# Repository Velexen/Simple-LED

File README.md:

# ESP-LED

A custom ESP32-based LED controller that integrates with Home Assistant over Wi-Fi. The device controls two independent LED strips and exposes them as separate light entities in Home Assistant, allowing full smart-home control.

## Purpose

The goal of this project is to build a DIY smart LED controller from scratch — including custom PCB hardware, firmware, and home automation integration — without relying on off-the-shelf solutions.

## Features

- Controls two independent LED strips
- Wi-Fi connectivity for remote control
- Home Assistant integration (appears as two distinct light entities)
- Main power switch and a strip-selector switch
- Custom 4-layer PCB design (schematics in [schematics/](schematics/))

## Hardware

The PCB was designed in Altium Designer. Design files are located in [schematics/ESP-LED/](schematics/ESP-LED/). A pinout reference sheet is available at [schematics/Pinout.xlsx](schematics/Pinout.xlsx).

Key components:
- ESP32 microcontroller
- MOSFETs for LED switching (see `MosFets.SchDoc`)
- 5V/12V power input (see `Power.SchDoc`)

## Firmware

Built with **ESP-IDF** (Espressif IoT Development Framework). Source code lives in [src/](src/).

A code rework is currently in work under the branch "code-redo"

## Getting Started

1. Install [ESP-IDF](https://docs.espressif.com/projects/esp-idf/en/latest/esp32/get-started/)
2. Clone this repo
3. Set your Wi-Fi credentials in `src/main/wifi.c`
4. Build and flash:
   ```
   idf.py build flash monitor
   ```

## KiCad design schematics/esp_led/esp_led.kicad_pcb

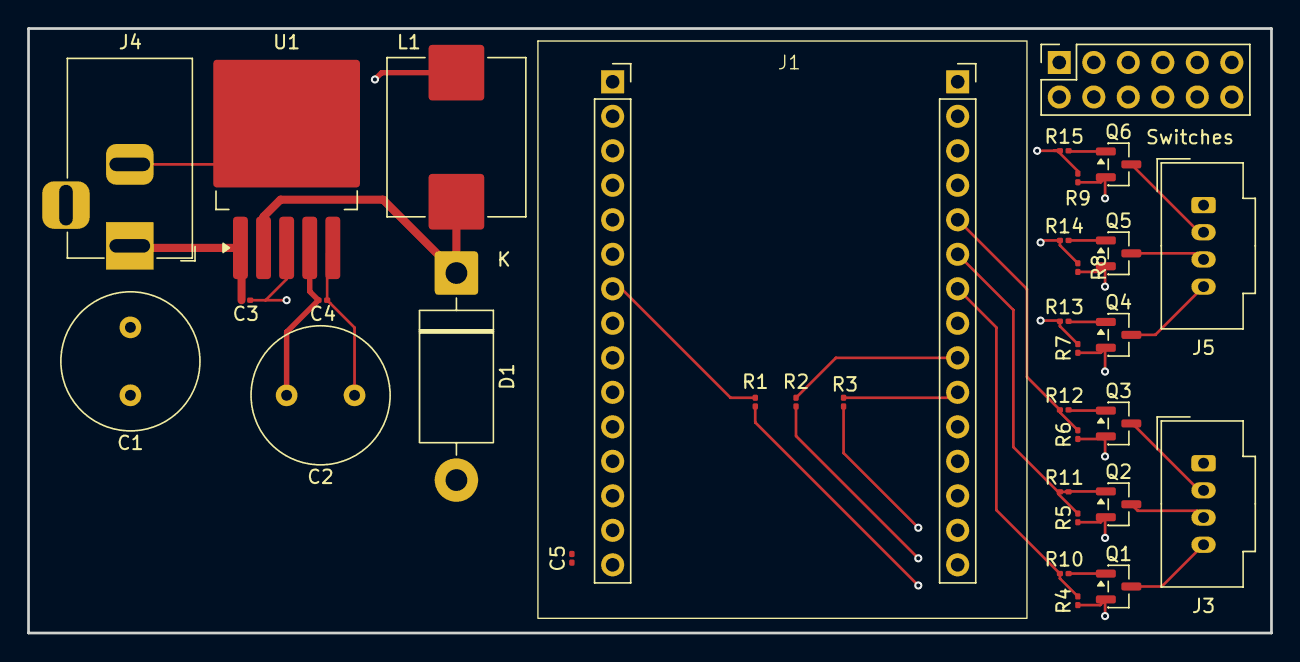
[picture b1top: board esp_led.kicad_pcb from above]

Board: 4 copper layers, 91.5 x 44.5 mm, 34 parts (0 on the bottom side), 27 nets.

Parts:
C1, C2: 470uF; C_Radial_D10.0mm_H16.0mm_P5.00mm
C3, C4, C5: 100nF; C_0201_0603Metric
D1: 1N5824; D_DO-201AD_P15.24mm_Horizontal
J1: ESP32-WROOM-DevKit; ESP32-32-Devkit-30-Pin
J3, J5: BOOMELE PH-4A; Molex_MicroClasp_55932-0430_1x04_P2.00mm_Vertical
J4: DC-005C-20A; BarrelJack_Horizontal
L1: 68μH; L_Sunlord_MWSA1005S
Q1, Q2, Q3, Q4, Q5, Q6: FDV303N; SOT-23
R1, R2, R3, R4, R5, R6, R7, R8, R9: 10kΩ; R_0201_0603Metric
R10, R11, R12, R13, R14, R15: 100Ω; R_0201_0603Metric
Switches: PinSocket_2x06_P2.54mm_Vertical
U1: LM2596S-5; TO-263-5_TabPin3

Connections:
+3V3: J1.16 (+3V3), R1.2, R2.2, R3.2, Switches.5, Switches.7, Switches.8, Switches.9, Switches.10
+5V: C2.1, C4.1, C5.1, J1.15 (VIN), L1.2, U1.4 (FB)
+24V: C1.1, C3.1, J4.1, Switches.11, U1.1 (VIN)
/Blue_1: J3.4, Q1.3 (D)
/Blue_2: J5.4, Q4.3 (D)
/Buck-Out: D1.1 (K), L1.1, U1.2 (OUT)
/Green_1: J3.2, Q3.3 (D)
/Green_2: J5.2, Q6.3 (D)
/Red_1: J3.3, Q2.3 (D)
/Red_2: J5.3, Q5.3 (D)
BLUE_PWM: J1.24 (IO18), R4.2, R10.1
BLUE_PWM_2: J1.10 (IO27), R7.2, R13.1
Color_Btn: J1.22 (IO17), R2.1
GND: C1.2, C2.2, C3.2, C4.2, C5.2, D1.2 (A), J1.14 (GND), J4.2, Q1.2 (S), Q2.2 (S), Q3.2 (S), Q4.2 (S), Q5.2 (S), Q6.2 (S), R4.1, R5.1, R6.1, R7.1, R8.1, R9.1, Switches.1, Switches.2, Switches.3, Switches.4, Switches.6, U1.3 (GND), U1.5 (~ON/OFF)
GREEN_PWM: J1.26 (IO21), R6.2, R12.1
GREEN_PWM_2: J1.8 (IO25), R9.2, R15.1
LED_24V: J3.1, J5.1, Switches.12
Main_Switch: J1.7 (IO33), R1.1
unnamed: Q1.1 (G), R10.2
unnamed: Q2.1 (G), R11.2
unnamed: Q3.1 (G), R12.2
unnamed: Q4.1 (G), R13.2
unnamed: Q5.1 (G), R14.2
unnamed: Q6.1 (G), R15.2
RED_PWM: J1.25 (IO19), R5.2, R11.1
RED_PWM_2: J1.9 (IO26), R8.2, R14.1
Selector_Sw: J1.21 (IO16), R3.1

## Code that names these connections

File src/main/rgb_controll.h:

#pragma once
#include <stdio.h>
#include "driver/ledc.h"
#include "esp_adc/adc_oneshot.h"

//OUTPUT 1
#define PIN_RED GPIO_NUM_21
#define CHANNEL_RED LEDC_CHANNEL_0
#define PIN_GREEN GPIO_NUM_19
#define CHANNEL_GREEN LEDC_CHANNEL_1
#define PIN_BLUE GPIO_NUM_18
#define CHANNEL_BLUE LEDC_CHANNEL_2

//OUTPUT 2
#define PIN_RED_2 GPIO_NUM_25
#define CHANNEL_RED_2 LEDC_CHANNEL_3
#define PIN_GREEN_2 GPIO_NUM_26
#define CHANNEL_GREEN_2 LEDC_CHANNEL_4
#define PIN_BLUE_2 GPIO_NUM_27
#define CHANNEL_BLUE_2 LEDC_CHANNEL_5

//INPUTS
#define MAIN_SWITCH GPIO_NUM_33
#define COLOR_BUTTON GPIO_NUM_17
#define SELECTOR_SWITCH GPIO_NUM_16

#define COLOR_POTENTIOMETER GPIO_NUM_34
#define COLOR_POTENTIOMETER_ADC_CHANNEL ADC_CHANNEL_6

#define BRIGHTNESS_POTENTIOMETER GPIO_NUM_35
#define BRIGHTNESS_POTENTIOMETER_ADC_CHANNEL ADC_CHANNEL_7

#define FREQUENCY 5000
#define RESOLUTION LEDC_TIMER_8_BIT

extern adc_oneshot_unit_handle_t adc1_handle;
extern ledc_channel_t led_channels[3];
extern ledc_channel_t led_channels_2[3];

void setupChannels(void);
void setDutyCycle(ledc_channel_t channel, uint32_t duty_cycle);
void setColorByRGB(uint8_t colors[3], ledc_channel_t led_channels[3], uint8_t brightness, bool light_on);

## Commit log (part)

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2026-01-27 I made the basic concept of what it is supposed to look like later. Which is not much but at least PWM works now via a potentiometer and button.
2026-01-29 Adding sleep after 60 seconds of downtime and separating the functions and declarations out of main. Also adding MosFETs to the schematic without connecting
2026-02-06 I implemented basic mqtt handling and wifi initialization. I also added a few things to the electrical schematic.
2026-02-06 Auto discovery in Home Assistant is now available. There are still some issues with how manual and remote are integrated together but that will be fixed once i actually finished working on the schema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
2026-02-08 I tried my best at implementing the Buck Converter correctly. The Code is not yet ready to allow the new pin usages and two different LED stripes
2026-02-09 The code now also supports two different LED stripes; with the addition of a main switch for turning of the lights and a selector switch to choose which of the two LED stripes to change. In addition 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
2026-02-13 The first draft of the PCB. I tried my best to do it kind of clean with 4 copper layers. I also moved the channel outputs for LED 1 a little to make pathing easier.
